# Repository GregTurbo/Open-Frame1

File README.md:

# Pummel Prism Pico (WIP)

An open-source All Button fight stick for traditional fighters, prioritizing small size and 3d printablitiy.

[FeralAI's code (gp2040)](https://github.com/FeralAI/GP2040)

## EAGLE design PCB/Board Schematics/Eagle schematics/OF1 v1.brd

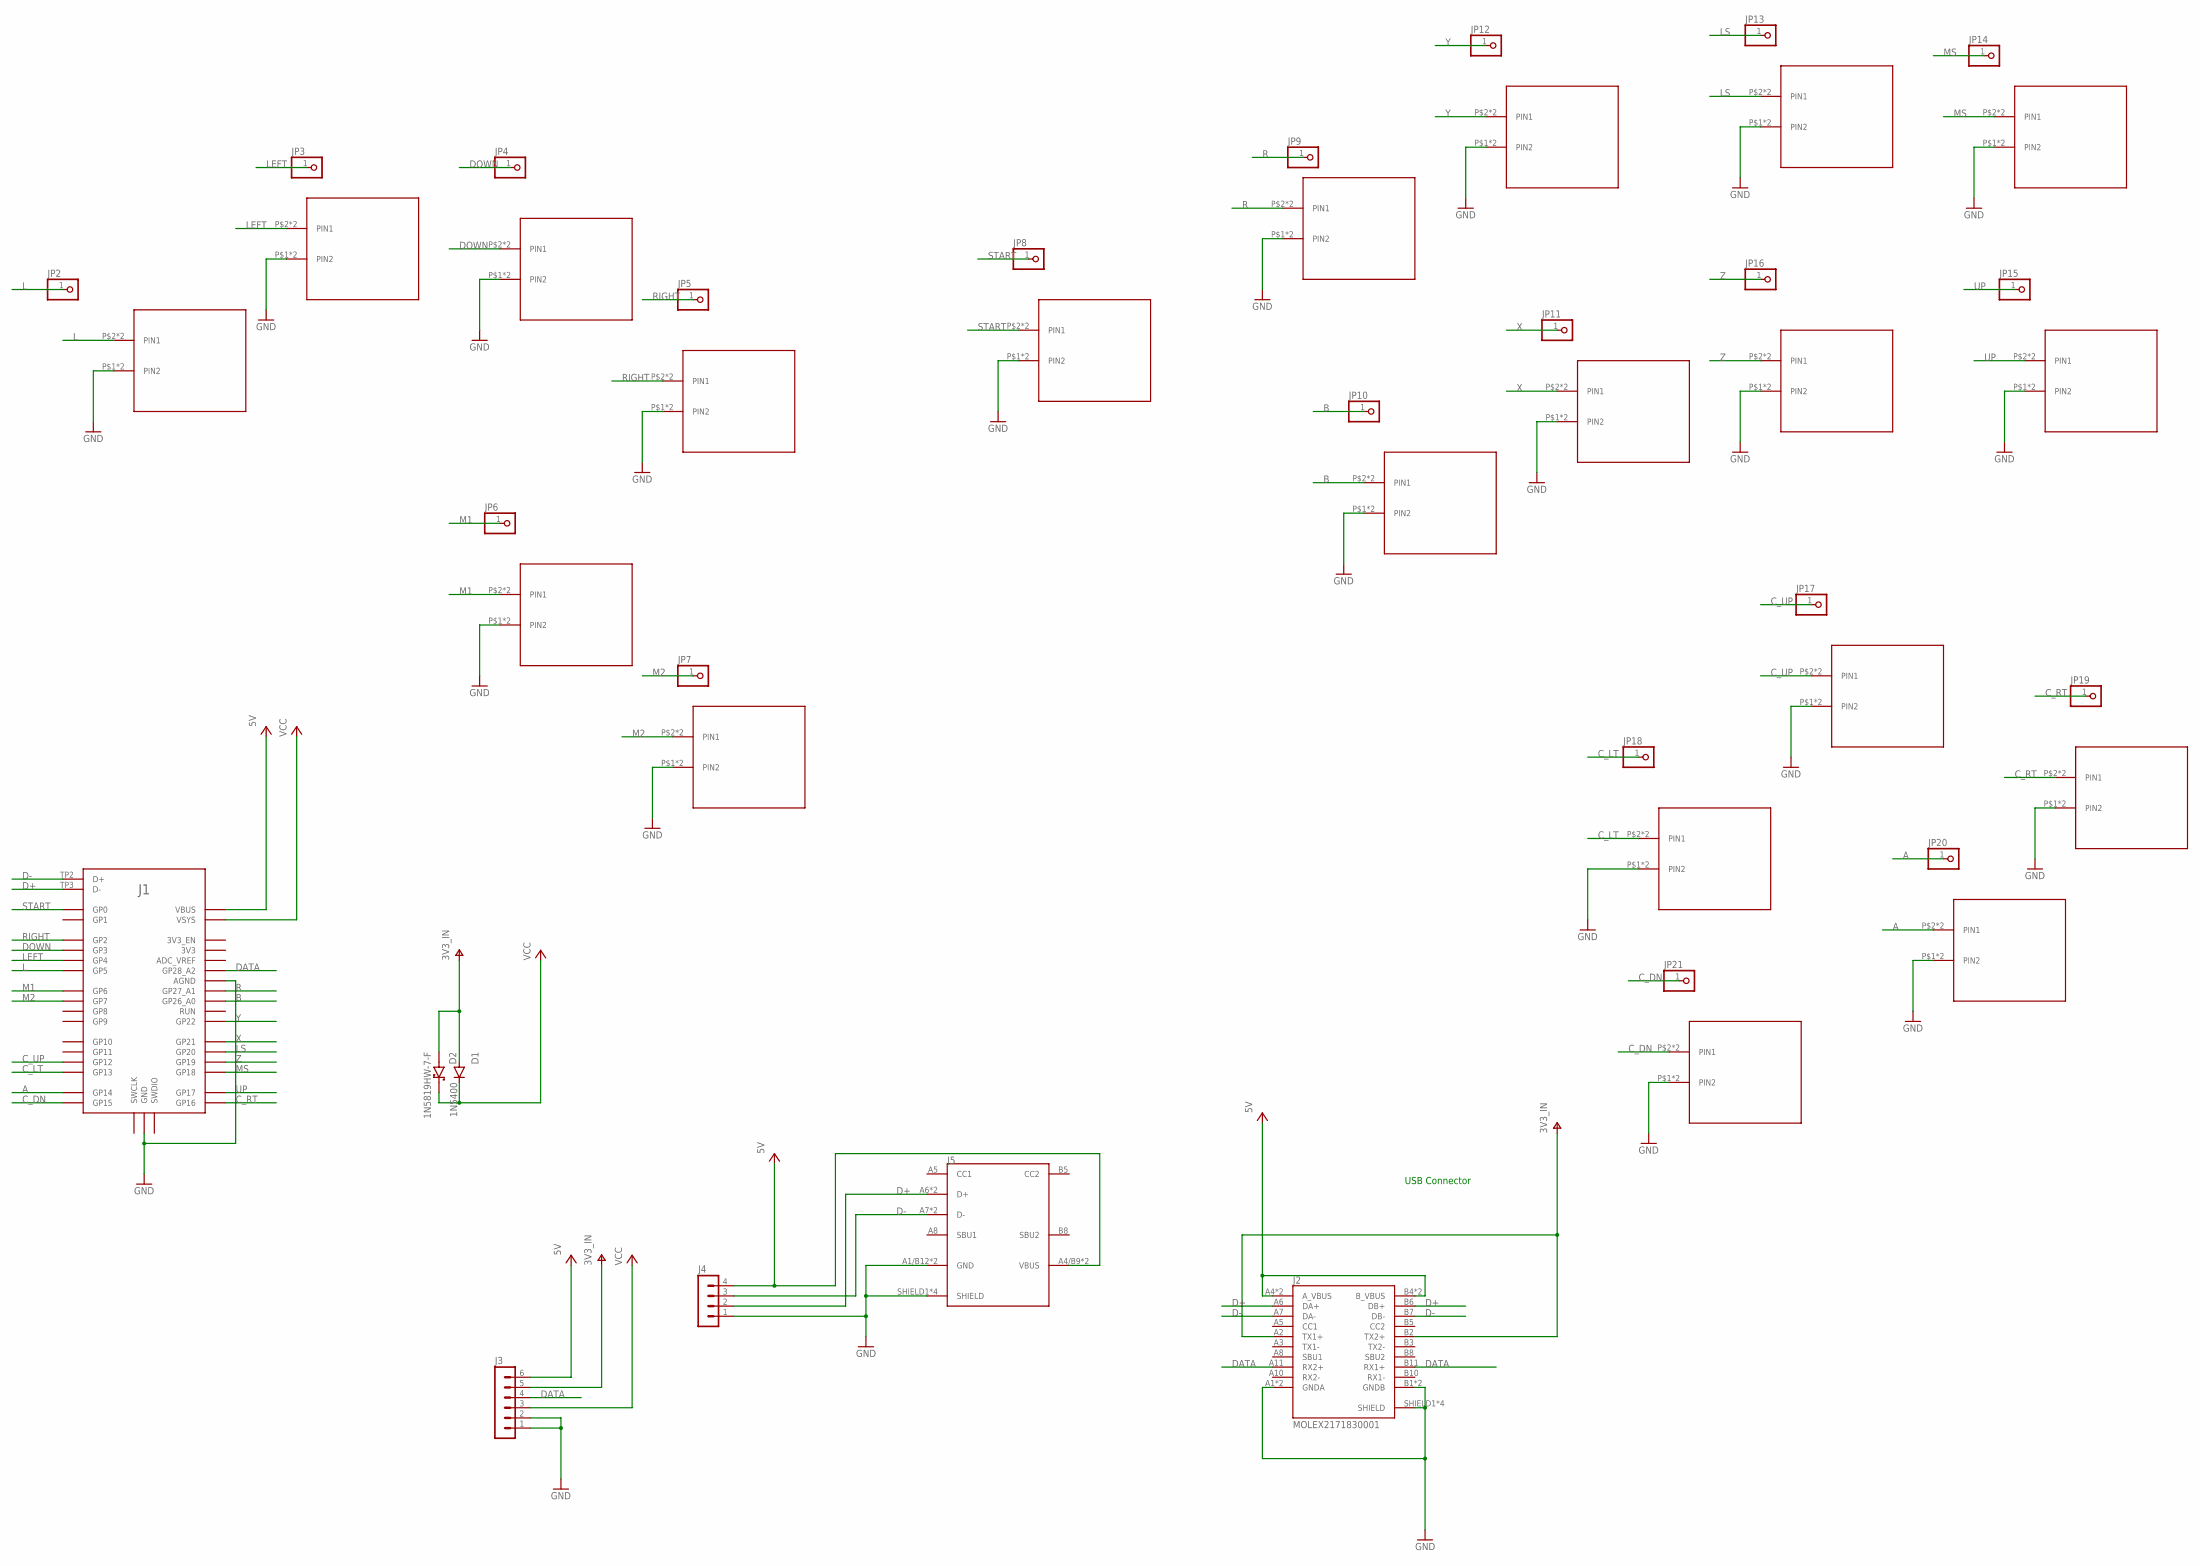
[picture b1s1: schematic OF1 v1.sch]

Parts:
D1: 1N5400; DO201-15
D2: 1N5819HW-7-F; SOD3715X145N
J1: RPI_PICO-TH; RPI_PICO_TH
J2: MOLEX2171830001; 24P
J3: MA06-1
J4: MA04-1
J5: GT-USB-7010ASV; 16P
JP2, JP3, JP4, JP5, JP6, JP7, JP8, JP9, JP10, JP11, JP12, JP13, JP14, JP15, JP16, JP17, JP18, JP19, JP20, JP21: PINHD-1X1; 1X01
U$1, U$2, U$4, U$5, U$6, U$7, U$8, U$9, U$10, U$11, U$12, U$13, U$14, U$15, U$16, U$17, U$18, U$19, U$20, U$21: MX-B; MX-BOTH

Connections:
+5V: J1.VBUS, J2.A4 (A_VBUS), J2.A9 (A_VBUS), J2.B4 (B_VBUS), J2.B9 (B_VBUS), J3.6, J4.4, J5.A4/B9 (VBUS), J5.B4/A9 (VBUS)
A: J1.GP14, JP20.1, U$20.P$2 (PIN1), U$20.P$3 (PIN1)
B: J1.GP26_A0, JP10.1, U$13.P$2 (PIN1), U$13.P$3 (PIN1)
C_DN: J1.GP15, JP21.1, U$21.P$2 (PIN1), U$21.P$3 (PIN1)
C_LT: J1.GP13, JP18.1, U$18.P$2 (PIN1), U$18.P$3 (PIN1)
C_RT: J1.GP16, JP19.1, U$19.P$2 (PIN1), U$19.P$3 (PIN1)
C_UP: J1.GP12, JP17.1, U$17.P$2 (PIN1), U$17.P$3 (PIN1)
D+: J1.TP3 (D-), J2.A6 (DA+), J2.B6 (DB+), J4.2, J5.A6 (D+), J5.B6 (D+)
D-: J1.TP2 (D+), J2.A7 (DA-), J2.B7 (DB-), J4.3, J5.A7 (D-), J5.B7 (D-)
DATA: J1.GP28_A2, J2.A11 (RX2+), J2.B11 (RX1+), J3.4
DOWN: J1.GP3, JP4.1, U$4.P$2 (PIN1), U$4.P$3 (PIN1)
GND: J1.AGND, J1.GND@1 (GND), J1.GND@2 (GND), J1.GND@3 (GND), J1.GND@4 (GND), J1.GND@5 (GND), J1.GND@6 (GND), J1.GND@7 (GND), J1.GND@8 (GND), J2.A1 (GNDA), J2.A12 (GNDA), J2.B1 (GNDB), J2.B12 (GNDB), J2.SHIELD1 (SHIELD), J2.SHIELD2 (SHIELD), J2.SHIELD3 (SHIELD), J2.SHIELD4 (SHIELD), J3.1, J3.2, J4.1, J5.A1/B12 (GND), J5.B1/A12 (GND), J5.SHIELD1 (SHIELD), J5.SHIELD2 (SHIELD), J5.SHIELD3 (SHIELD), J5.SHIELD4 (SHIELD), U$1.P$1 (PIN2), U$1.P$4 (PIN2), U$2.P$1 (PIN2), U$2.P$4 (PIN2), U$4.P$1 (PIN2), U$4.P$4 (PIN2), U$5.P$1 (PIN2), U$5.P$4 (PIN2), U$6.P$1 (PIN2), U$6.P$4 (PIN2), U$7.P$1 (PIN2), U$7.P$4 (PIN2), U$8.P$1 (PIN2), U$8.P$4 (PIN2), U$9.P$1 (PIN2), U$9.P$4 (PIN2), U$10.P$1 (PIN2), U$10.P$4 (PIN2), U$11.P$1 (PIN2), U$11.P$4 (PIN2), U$12.P$1 (PIN2), U$12.P$4 (PIN2), U$13.P$1 (PIN2), U$13.P$4 (PIN2), U$14.P$1 (PIN2), U$14.P$4 (PIN2), U$15.P$1 (PIN2), U$15.P$4 (PIN2), U$16.P$1 (PIN2), U$16.P$4 (PIN2), U$17.P$1 (PIN2), U$17.P$4 (PIN2), U$18.P$1 (PIN2), U$18.P$4 (PIN2), U$19.P$1 (PIN2), U$19.P$4 (PIN2), U$20.P$1 (PIN2), U$20.P$4 (PIN2), U$21.P$1 (PIN2), U$21.P$4 (PIN2)
L: J1.GP5, JP2.1, U$1.P$2 (PIN1), U$1.P$3 (PIN1)
LEFT: J1.GP4, JP3.1, U$2.P$2 (PIN1), U$2.P$3 (PIN1)
LS: J1.GP20, JP13.1, U$11.P$2 (PIN1), U$11.P$3 (PIN1)
M1: J1.GP6, JP6.1, U$6.P$2 (PIN1), U$6.P$3 (PIN1)
M2: J1.GP7, JP7.1, U$7.P$2 (PIN1), U$7.P$3 (PIN1)
MS: J1.GP18, JP14.1, U$12.P$2 (PIN1), U$12.P$3 (PIN1)
R: J1.GP27_A1, JP9.1, U$9.P$2 (PIN1), U$9.P$3 (PIN1)
RIGHT: J1.GP2, JP5.1, U$5.P$2 (PIN1), U$5.P$3 (PIN1)
START: J1.GP0, JP8.1, U$8.P$2 (PIN1), U$8.P$3 (PIN1)
UP: J1.GP17, JP15.1, U$16.P$2 (PIN1), U$16.P$3 (PIN1)
V+: D1.A, D2.A, J2.A2 (TX1+), J2.B2 (TX2+), J3.5
VCC: D1.C, D2.C (K), J1.VSYS, J3.3
X: J1.GP21, JP11.1, U$14.P$2 (PIN1), U$14.P$3 (PIN1)
Y: J1.GP22, JP12.1, U$10.P$2 (PIN1), U$10.P$3 (PIN1)
Z: J1.GP19, JP16.1, U$15.P$2 (PIN1), U$15.P$3 (PIN1)

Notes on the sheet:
USB Connector

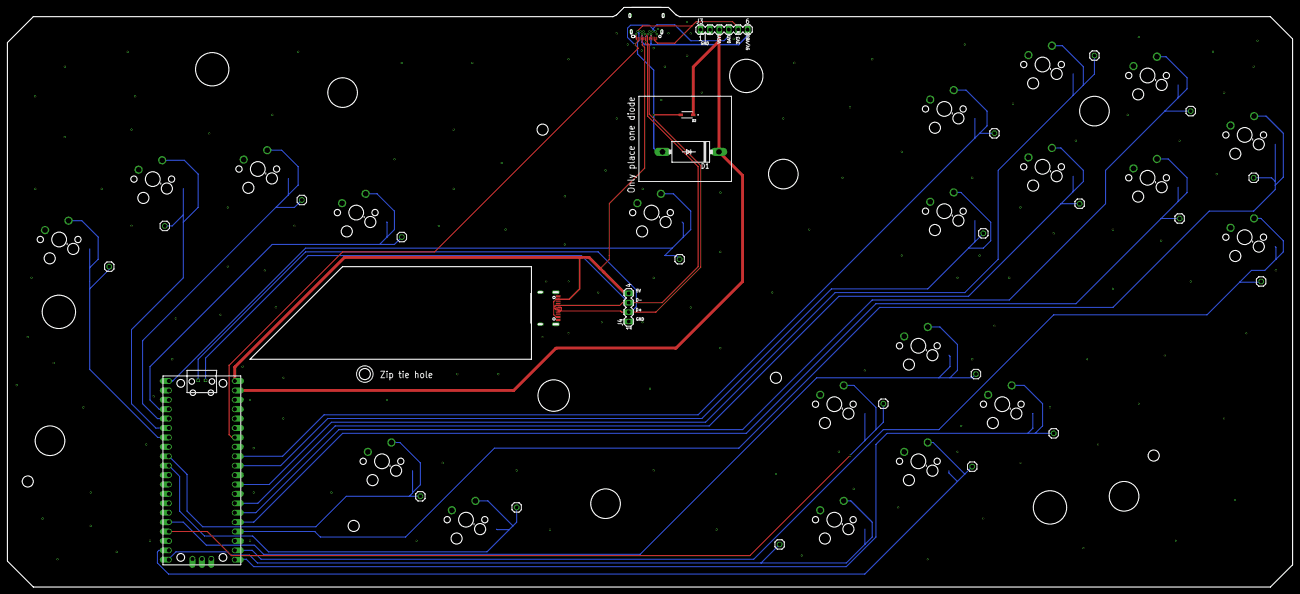
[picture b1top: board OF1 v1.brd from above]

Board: 2 copper layers, 347.0 x 156.5 mm, 47 parts (0 on the bottom side), 27 nets.

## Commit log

2022-06-04 added readme, no images yet
2022-06-15 added images
2022-06-17 Fixed the BOM
2022-08-11 Added Kicad version
    Moved to Kicad to avoid slotted hole issues with JLC
2022-10-10 Wip COMMIT
2022-10-11 adding usbc support to the pcb. Updating fab files to reflect
2023-02-01 checked to make sure all files are good
2023-02-14 feat: tonberry mod
2023-04-12 added ordering guide
2023-04-12 adding updated fab files
2023-04-13 added case Read Me
2024-02-11 1.04, new hotswap socket footprint
